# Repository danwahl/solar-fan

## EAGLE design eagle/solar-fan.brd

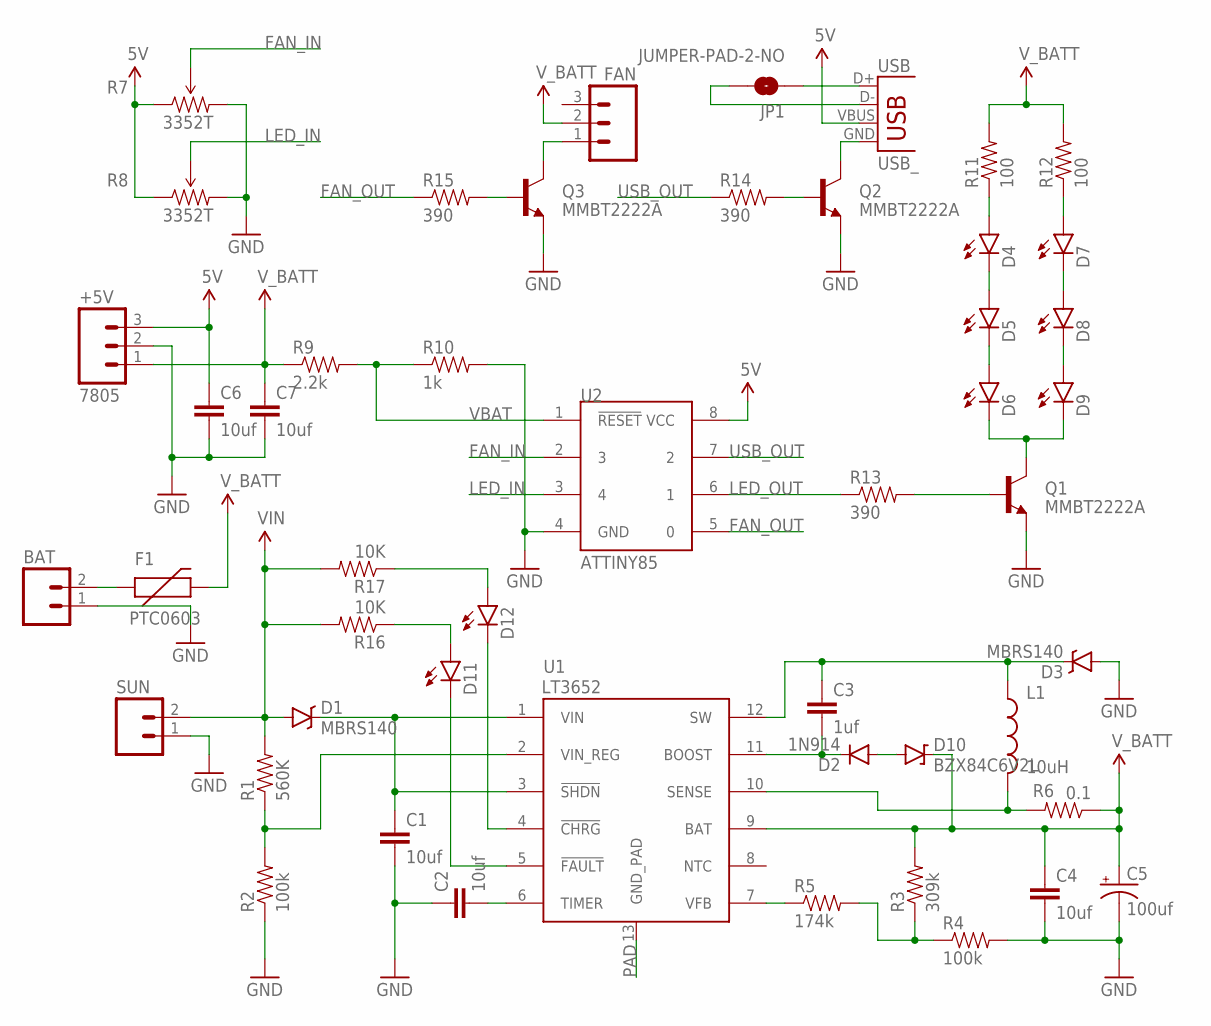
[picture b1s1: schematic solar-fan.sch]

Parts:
+5V: 7805; 1X03
BAT: M025MM; SCREWTERMINAL-5MM-2
C1, C2, C4, C6, C7: 10uf; 0603-CAP
C3: 1uf; 0603-CAP
C5: 100uf; CPOL-RADIAL-100UF-25V
D1, D3: MBRS140; SMA-DIODE
D2: 1N914; SOD-323
D4, D5, D6, D7, D8, D9, D11, D12: LED-WHITE0603; LED-0603
D10: BZX84C6V2L; SOT23-3
F1: PTC0603; 0603
FAN: M03POLAR; MOLEX-1X3
JP1: JUMPER-PAD-2-NO; PAD-JUMPER-2-NO_NO_SILK
L1: 10uH; RLB0912
Q1, Q2, Q3: MMBT2222A; SOT23-3
R1: 560K; 0603-RES
R2, R4: 100k; 0603-RES
R3: 309k; 0603-RES
R5: 174k; 0603-RES
R6: 0.1; 0603-RES
R7, R8: 3352T
R9: 2.2k; 0603-RES
R10: 1k; 0603-RES
R11, R12: 100; 0603-RES
R13, R14, R15: 390; 0603-RES
R16, R17: 10K; 0603-RES
SUN: M025MM; SCREWTERMINAL-5MM-2
U1: LT3652; MSOP-12_GND
U2: ATTINY85; 8P3
USB: USB_; USB-A-S-SILK-FEMALE

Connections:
5V: +5V.3, C6.1, R7.CCW, R8.CCW, U2.8 (VCC), USB.VBUS
BOOST: C3.2, D2.C, U1.11 (BOOST)
FAN_IN: R7.WIPER, U2.2 (3)
FAN_OUT: R15.1, U2.5 (0)
GND: +5V.2, BAT.1, C1.2, C2.1, C4.2, C5.2 (-), C6.2, C7.2, D3.A, Q1.2 (E), Q2.2 (E), Q3.2 (E), R2.1, R4.2, R7.CW, R8.CW, R10.2, SUN.1, U2.4 (GND)
LED_IN: R8.WIPER, U2.3 (4)
LED_OUT: R13.1, U2.6 (1)
unnamed: Q1.1 (B), R13.2
unnamed: Q2.1 (B), R14.2
unnamed: Q3.1 (B), R15.2
unnamed: FAN.1, Q3.3 (C)
unnamed: R3.1, R4.1, R5.2
unnamed: JP1.1, USB.D+
unnamed: JP1.2, USB.D-
unnamed: D2.A, D10.1 (A)
unnamed: D12.A, R17.1
unnamed: D12.C, U1.4 (!CHRG)
unnamed: D4.A, R11.1
unnamed: D7.A, R12.1
unnamed: D4.C, D5.A
unnamed: D7.C, D8.A
unnamed: D5.C, D6.A
unnamed: D8.C, D9.A
unnamed: D6.C, D9.C, Q1.3 (C)
unnamed: D11.C, U1.5 (!FAULT)
unnamed: Q2.3 (C), USB.GND
unnamed: D11.A, R16.1
unnamed: BAT.2, F1.1
PAD: U1.13 (GND_PAD)
SENSE: L1.2, R6.2, U1.10 (SENSE)
SHDN: C1.1, D1.C, U1.1 (VIN), U1.3 (!SHDN)
SW: C3.1, D3.C, L1.1, U1.12 (SW)
TIMER: C2.2, U1.6 (TIMER)
USB_OUT: R14.1, U2.7 (2)
VBAT: R9.2, R10.1, U2.1 (!RESET)
VFB: R5.1, U1.7 (VFB)
VIN: D1.A, R1.2, R16.2, R17.2, SUN.2
VIN_REG: R1.1, R2.2, U1.2 (VIN_REG)
V_BATT: +5V.1, C4.1, C5.1 (+), C7.1, D10.3 (C), F1.2, FAN.2, R3.2, R6.1, R9.1, R11.2, R12.2, U1.9 (BAT)

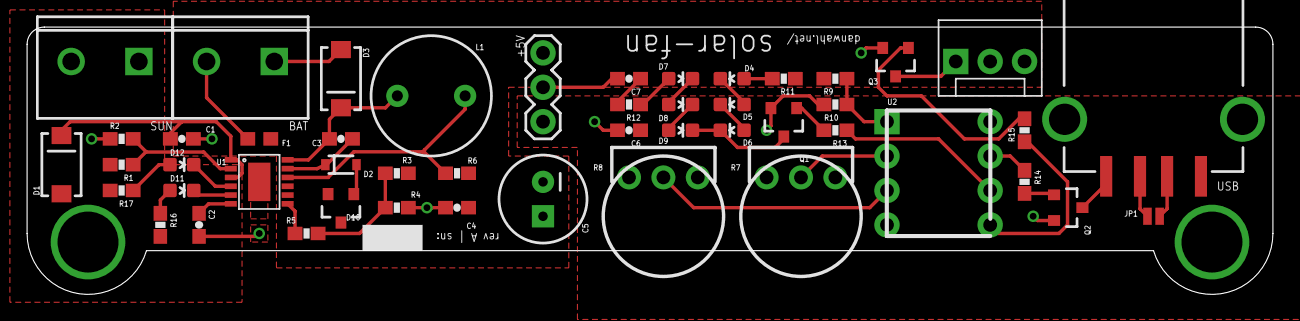
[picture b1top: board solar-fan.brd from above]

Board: 2 copper layers, 92.0 x 19.7 mm, 49 parts (0 on the bottom side), 38 nets.

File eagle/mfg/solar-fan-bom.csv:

"Qty";"Value";"Device";"Package";"Parts";"Description";"PN";"PN2";"PROD_ID";"STOREFRONT_ID";"VALUE";
"1";"";"LED-WHITE0603";"LED-0603";"D11";"White SMD LEDs";"160-1436-1-ND";"";"DIO-09004";"";"";
"1";"";"LED-WHITE0603";"LED-0603";"D12";"White SMD LEDs";"160-1437-1-ND";"";"DIO-09004";"";"";
"6";"";"LED-WHITE0603";"LED-0603";"D4, D5, D6, D7, D8, D9";"White SMD LEDs";"1516-1057-1-ND";"";"DIO-09004";"";"";
"2";"";"M025MM";"SCREWTERMINAL-5MM-2";"BAT, SUN";"Standard 2-pin 0.1" header. Use with";"277-1667-ND";"";"";"PRT-08432";"";
"1";"";"M03POLAR";"MOLEX-1X3";"FAN";"Header 3";"WM4201-ND";"";"";"";"";
"1";"0.1";"RESISTOR0603-RES";"0603-RES";"R6";"Resistor";"1276-6155-1-ND";"";"";"";"";
"2";"100";"RESISTOR0603-RES";"0603-RES";"R11, R12";"Resistor";"P100HCT-ND";"";"";"";"";
"2";"100k";"RESISTOR0603-RES";"0603-RES";"R2, R4";"Resistor";"P100KHCT-ND";"";"";"";"";
"1";"100uf";"CAP_POLPTH1";"CPOL-RADIAL-100UF-25V";"C5";"Capacitor Polarized";"399-6650-1-ND";"";"";"";"";
"2";"10K";"RESISTOR0603-RES";"0603-RES";"R16, R17";"Resistor";"P10KGCT-ND";"";"";"";"";
"1";"10uH";"INDUCTORRLB0912";"RLB0912";"L1";"Inductors";"RLB0912-100KL-ND";"";"";"";"";
"5";"10uf";"CAP0603-CAP";"0603-CAP";"C1, C2, C4, C6, C7";"Capacitor";"490-7202-1-ND";"";"";"";"";
"1";"174k";"RESISTOR0603-RES";"0603-RES";"R5";"Resistor";"P174KHCT-ND";"";"";"";"";
"1";"1N914";"DIODEBAS16";"SOD-323";"D2";"Diode";"1N914BWSCT-ND";"";"DIO-09646";"";"250mA/100V";
"1";"1k";"RESISTOR0603-RES";"0603-RES";"R10";"Resistor";"P1.00KHCT-ND";"";"";"";"";
"1";"1uf";"CAP0603-CAP";"0603-CAP";"C3";"Capacitor";"490-1536-1-ND";"";"";"";"";
"1";"2.2k";"RESISTOR0603-RES";"0603-RES";"R9";"Resistor";"P2.20KHCT-ND";"";"";"";"";
"1";"309k";"RESISTOR0603-RES";"0603-RES";"R3";"Resistor";"P309KHCT-ND";"";"";"";"";
"2";"3352T";"3352T";"3352T";"R7, R8";"";"3352T-103LF-ND";"";"";"";"";
"3";"390";"RESISTOR0603-RES";"0603-RES";"R13, R14, R15";"Resistor";"P390HCT-ND";"";"";"";"";
"1";"560K";"RESISTOR0603-RES";"0603-RES";"R1";"Resistor";"P560KGCT-ND";"";"";"";"";
"1";"7805";"M03PTH";"1X03";"+5V";"Header 3";"811-2196-5-ND";"LM7805CT-ND";"";"";"";
"1";"ATTINY85";"ATTINY85";"8P3";"U2";"";"ATTINY85-20PU-ND";"AE9986-ND";"";"";"";
"1";"BZX84C6V2L";"BZX84C6V2L";"SOT23-3";"D10";"";"SZBZX84C6V2LT1GOSCT-ND";"";"";"";"";
"1";"JUMPER-PAD-2-NO";"JUMPER-PAD-2-NO";"PAD-JUMPER-2-NO_NO_SILK";"JP1";"";"";"";"";"";"";
"1";"LT3652";"LT3652";"MSOP-12_GND";"U1";"LT3652 MPPT Solar Charge Controller";"LT3652EMSE#PBF-ND";"";"";"";"LT3652";
"2";"MBRS140";"DIODE-SCHOTTKY-MBRA140";"SMA-DIODE";"D1, D3";"Schottky diodes in SFE's production catalog";"MBRS140T3GOSCT-ND";"";"DIO-08053";"";"MBRA140";
"3";"MMBT2222A";"TRANSISTOR_NPNMMBT2222A";"SOT23-3";"Q1, Q2, Q3";"Generic NPN BJT";"MMBT2222AFSCT-ND";"";"TRANS-08049";"";"MMBT2222A";
"1";"PTC0603";"PTC0603";"0603";"F1";"Resettable Fuse PTC";"SF-0603S200-2CT-ND";"";"";"";"";
"1";"USB_";"USB_";"USB-A-S-SILK-FEMALE";"USB";"USB Connectors";"1175-1001-ND";"";"";"";"";

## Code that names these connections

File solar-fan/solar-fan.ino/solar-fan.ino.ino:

#include <avr/sleep.h>
#include <avr/wdt.h>
#include <avr/power.h>

// hardware definitions
#define VBAT_PIN      A0              // also reset pin
#define VBAT_SLOPE    3.24889         // x/1e3 = (y - x)/2.2e3 + (5 - x)/45e3
#define VBAT_OFFSET   -0.244444
#define VBAT_MIN      10.5f
#define VBAT_NOM      12.0f           // should be greater than VBAT_MIN
#define FAN_IN_PIN    A3
#define FAN_OUT_PIN   0
#define LED_IN_PIN    A2
#define LED_OUT_PIN   1
#define USB_OUT_PIN   2

// system states
enum {RUN, LOWBAT};

// global vars
float vbat;
unsigned fan_in, led_in, fan_out, led_out, usb_out, state;

/***************************************************************************
 * watchdog timer isr
 **************************************************************************/
ISR(WDT_vect) {
}

/***************************************************************************
 * setup
 **************************************************************************/
void setup() {
  // set tmr0 pwm frequency to 8e6/2^8/psc
  TCCR0B &= ~(_BV(CS01) | _BV(CS02));
  TCCR0B |= _BV(CS00);

  // usb out pin setup
  pinMode(USB_OUT_PIN, OUTPUT);

  // disable outputs
  analogWrite(FAN_OUT_PIN, 0);
  analogWrite(LED_OUT_PIN, 0);
  digitalWrite(USB_OUT_PIN, LOW);

  // go to run
  state = RUN;
}

/***************************************************************************u
 * loop
 **************************************************************************/
void loop() {
  // read inputs
  vbat = ((float)analogRead(VBAT_PIN)*5.0f/1023.0f)*VBAT_SLOPE + VBAT_OFFSET;
  fan_in = analogRead(FAN_IN_PIN);
  led_in = analogRead(LED_IN_PIN);

  /*// map inputs to outputs
  fan_out = map(fan_in, 0, 1023, 0, 255);
  led_out = map(led_in, 0, 1023, 0, 255);
  usb_out = HIGH;

  // write outputs
  analogWrite(FAN_OUT_PIN, fan_out);
  analogWrite(LED_OUT_PIN, led_out);
  digitalWrite(USB_OUT_PIN, usb_out);

  // idle for a bit
  sleep_system(SLEEP_MODE_IDLE, WDTO_1S);
  //delay(1000);*/

  switch (state) {
    case (RUN):
      // check if vbat below min voltage threshold
      if (vbat < VBAT_MIN) {
        // set outputs
        fan_out = led_out = 0;
        usb_out = LOW;

        // disable outputs
        analogWrite(FAN_OUT_PIN, fan_out);
        analogWrite(LED_OUT_PIN, led_out);
        digitalWrite(USB_OUT_PIN, usb_out);

        // set state
        state = LOWBAT;

        // sleep for a while
        sleep_system(SLEEP_MODE_PWR_DOWN, WDTO_8S);
      }
      else {
        // map inputs to outputs
        fan_out = map(fan_in, 0, 1023, 0, 255);
        led_out = map(led_in, 0, 1023, 0, 255);
        usb_out = HIGH;

        // write outputs
        analogWrite(FAN_OUT_PIN, fan_out);
        analogWrite(LED_OUT_PIN, led_out);
        digitalWrite(USB_OUT_PIN, usb_out);

        // idle for a bit
        delay(100);
      }
      break;
    case (LOWBAT):
      // back to run if vbat nominal
      if (vbat >= VBAT_NOM) {
        state = RUN;

        // idle for a bit
        delay(100);
      }
      // otherwise sleep again
      else sleep_system(SLEEP_MODE_PWR_DOWN, WDTO_8S);
      break;
    default:
      state = RUN;
      break;
  }
}

/***************************************************************************
 * sleep system
 **************************************************************************/
void sleep_system(unsigned mode, unsigned wdto) {
  // disable peripherals
  power_timer1_disable();
  power_adc_disable();

  // set sleep mode
  set_sleep_mode(mode);
  sleep_enable();

  // set watchdog and sleep
  setup_watchdog(wdto);
  sleep_mode();

  // zzzzz... (sleeping here)

  // disable sleep
  sleep_disable();

  // enable peripherals
  power_adc_enable();
  power_timer1_enable();
}

/***************************************************************************
 * watchdog setup
 **************************************************************************/
void setup_watchdog(unsigned wdto) {
  // Limit incoming amount to legal settings
  if (wdto > WDTO_8S) wdto = WDTO_8S;

  // Set the special 5th bit if necessary
  byte bb = wdto & 0x07;
  if (wdto > 7) bb |= (1 << 5);

  MCUSR &= ~(1 << WDRF);              // Clear the watchdog reset
  WDTCR |= (1 << WDCE) | (1 << WDE);  // Set WD_change enable, set WD enable
  WDTCR = bb;                         // Set new watchdog timeout value
  WDTCR |= _BV(WDIE);                 // Set the interrupt enable, this will keep unit from resetting after each int
}

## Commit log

2016-08-16 adding arduino test project
2016-08-16 switching sensors
2016-09-12 eagle initial commit, schematic only
2016-09-14 first draft of board layout, minor schematic fixes
2016-09-15 minor layout updates, adding PNs to schematic
2016-09-17 layout update, bom, components
2016-09-18 updated fan connector and layout, silk screen, mfg files
2016-09-18 changed pn for c1 and c4
2016-09-19 rev - build
2016-09-26 solar fan firmware first draft
2016-10-13 - updated charge voltage - led/cap placement - proper fan vs. usb out on micro - changed transistors to smd - solder mask change for gnd pad - added status leds for chager - changed battery/solar con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
2016-10-17 rev A build
2016-11-07 solar fan sw initial commit, rev A
2016-11-08 solar fan working, no idle, 8 MHz
2016-11-14 fix for idle, file structure for arduino code
2016-11-28 minor electronics/software updates, still rev A

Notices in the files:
parts and their libraries:
SparkFun-PowerIC: Licensing: Creative Commons ShareAlike 4.0 International - https://creativecommons.org/licenses/by-sa/4.0
